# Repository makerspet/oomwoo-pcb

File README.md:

<div align="center">

# OOMWOO I/O Board

*Open-source robot vacuum you build yourself.*

STM32G473 MCU · Motor drivers · Sensors · 4S charging · Smartphone compute (v1) · Raspberry Pi CM4/CM5 (planned) · KiCad

</div>

Part of [OOMWOO open-source robot vacuum](https://github.com/makerspet/oomwoo) project.

Get [MCU firmware](https://github.com/makerspet/oomwoo-firmware/).

## Two boards

I'm keeping the first board as simple as possible, so it can be built and tested sooner:

- **[`kicad/main-phone`](kicad/main-phone/README.md) - v1, in progress.** An Android phone is the compute, connected to the STM32 over USB-C. No Raspberry Pi, cameras, M.2, SD card, speaker or mopping. The STM32 runs every motor and sensor, including the LiDAR and the front ToF sensors, and forwards their data to the phone.
- **[`kicad/main`](kicad/main) - Raspberry Pi CM4/CM5 carrier, planned.** The Pi is still in the plans: cameras, an NPU and always-on Wi-Fi come with it. The notes below describe this board.

Details for both are in the [I/O board spec](docs/SPEC.md). Symbol, footprint and 3D libraries shared by all boards are in [`kicad/lib`](kicad/lib). Each board folder keeps its schematic PDF and BOM in `output/`, e.g. [the v1 board schematic](kicad/main-phone/output/Main.pdf).

The v1 board comes with a **[charging-only dock](kicad/charging-dock/README.md)**: a 20 V brick, a CH32V003 MCU (Arduino core, ch32fun, PlatformIO), robot detection before the contacts go live, and an IR beacon. The plan is to make the v1 board, the dock and the small sensor boards (including the two [front ToF boards](kicad/front-sensors/README.md), one design fitted twice, the [side sensor board](kicad/side-sensors/README.md) six [cliff sensor boards](kicad/cliff-sensor/README.md), the [rear docking IR board](kicad/rear-ir/README.md) and two [Hall sensor boards](kicad/hall-sensor/README.md)) as one panel (V-cuts or mouse bites), so they share parts and cost less to make and ship. To keep part references unique across boards, every board has its own reference range: main board 1-999, dock 1000s, front ToF 2000s, side sensor 3000s, cliff 4000s, rear IR 5000s, Hall 6000s.

## Architecture notes

Consumer vacuums typically split compute into CPU and MCU. The MCU ([real examples](https://robotinfo.dev/)) controls
- all motors - driving wheels, suction fan, side brushes, mop motors, mop lift servos, pump and so on
- all sensors except below - IR cliff, IR side proximity, IR docking, wheel drop, bumper (IR or micro-switches), motor encoders, ultrasonic carpet sensor
- all push buttons
- 2D LiDAR motor RPM
- power - battery charging, motors power on/off
- all safety sensors - overcurrent for all motors (cheap vacuums ignore overcurrent sensing)

I/O board also provides audio encoders/decoders, amp, speaker (connector), mics (if any).

CPU receives
- 2D LiDAR data over serial port
- IMU (sometimes IMU gets forwarded via MCU) over SPI/I2C
- cameras (2x MIPI for visual obstacle avoidance)

MCU (and CPU) are usually always active. This allows the user to start cleaning at any time (especially via app remotely). Exceptions:
- no power (battery dead and no dock power)
- user explicitly shut down the vacuum by long-pressing the power button

The MCU's overarching constraint is to ensure robot safety. This is necessary to pass CE mark tests. Here is how MCU ensures safety:
- MCU firmware uses FreeRTOS or similar, static memory allocation, watchdog, guaranteed reaction time
- MCU acts as watchdog for CPU, resets CPU if CPU becomes unresponsive
- MCU connects to CPU over serial using a custom serial protocol ([concrete example](https://github.com/codetiger/VacuumRobot)). No micro-ROS to reduce dependencies, prevent bugs from updated 3rd party libraries slipping into safety-critical MCU firmware.
- MCU shuts down some (or all) motors when MCU detects overcurrent (brush stuck)
- MCU shuts down all motors (including power to all motors) when CPU becomes unresponsive (to prevent CPU sending garbage commands to MCU)
- MCU monitors battery charging, shuts it down when needed (battery too hot)
- MCU stops driving wheel motors when bumper sensors activate
- MCU tests motors, sensors
- MCU does not depend on CPU
- MCU toggles watchdog GPIO; otherwise an external-to-MCU circuit shuts down motor power

Consumer vacuums place CPU and MCU on the same PCB board. Since OOMWOO has to be hackable, it seems best to separate I/O from the compute. Therefore, this I/O board needs to have
- MCU and programming header
  - STM32G473VCT6 (LQFP-100): enough GPIOs, timers and ADCs for every motor and sensor, built-in op-amps for the carpet sensor echo, a USB device port and an RTC, in a hand-solderable package
  - see the [I/O board spec](docs/SPEC.md)
- all vacuum motor drivers (with connectors), driven by the MCU
  - cliff, side proximity, docking, bumper, carpet, water tank full/empty, dust bin present, motor overcurrent, motor encoders
- MCU connected to all sensors (except those handled by CPU like LiDAR serial, MIPI cameras I/O, IMU); sensor connectors
- control circuit for 2D LiDAR's motor (controlled by MCU)
- battery charging, power management (motors power on/off, charging on/off, power shut down), power for CPU compute module (see below)
- push buttons (home, power, etc.) and UI LEDs
- dock connector (dock power, sense dock present)
- USB power for charging; USB for serial shell, etc.
- audio encoder/decoder, audio amp, mics (if any)
- SD card for hacking, cheap large storage
- connect IMU FSYNC to MCU to synchronize MCU timestamps with IMU data streaming to CPU

Consumer vacuums usually don't have a CPU fan/heatsink because the vacuum's suction fan can (indirectly) cool the CPU/MCU PCB. Therefore, no CPU fan on this I/O board.

As far as compute - currently it seems best to use a Raspberry Pi CM4/CM5 compute module. Why?
- CM4/CM5 modules cost a bit less than a full Raspberry Pi 4/5
- CM4/CM5 have lower profile/height vs a full Raspberry Pi 4/5, important to keep vacuum cleaner slim
- there are plenty of 3rd party compute modules pin-compatible with CM4/CM5, making the compute swappable, hackable
  - 3rd party compute modules with NPUs are especially interesting because we need NPU for real-time camera-based obstacle detection

Compute module headers should expose
- 2x MIPI camera I/O
- 1x serial for CPU-MCU comms
- 1x serial for CPU-LiDAR comms
- 1x SPI (or I2C) for CPU-IMU comms
- audio (digital?) I/O
- power from I/O board to CM
- a few TBD GPIOs
  - MCU GPIO to reset CPU

This board should be designed using an open-source PCB tool (KiCad seems like a good choice).

## No manufacturing support

These designs are shared as-is, for reference and for your own work. I don't support manufacturing them: I can't help with ordering (JLCPCB or otherwise), out-of-stock parts, part substitutions, or troubleshooting boards built by others.

## License

[Apache License 2.0](LICENSE).

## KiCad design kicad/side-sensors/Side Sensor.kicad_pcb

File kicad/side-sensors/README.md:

# OOMWOO side sensor board

A small board on the robot's right side, for wall-following and for spotting the dock while driving past it. It plugs into the [main board](../main-phone/README.md) (SIDE-R1) with a 7-pin cable. Rev 2, 2026-10-27. There is no left side sensor on v1.

Rev 1 had a VL6180 with a 2.8 V regulator and a TSOP38238. The VL6180 is NRND at ST (obsolete at DigiKey and Future), and its 2.8 V I/O sits at its limit on the robot's 3.3 V bus.

## Circuit

- U3001: VL53L0X (VL53L0CXV0DH/1, LCSC C91199, ~$1.63): single-zone time-of-flight distance sensor, runs from 3.3 V directly.
  - It reads poorly below ~3 cm, so the board sits a little recessed in the robot's side.
  - 10 µF + 100 nF (C3001/C3002) at its supply pins.
  - XSHUT has no pull-up since 2026-11-04 (R3001 removed): the MCU drives it (PE3), and the sensor rail is off whenever the MCU is in reset. GPIO1 (open drain, the interrupt) has no pull-up here since 2026-11-03: it joins the shared INT-SENSORS line on the main board, pulled up there by R2 (47k; R61 until 2026-11-11), so R3002 was in parallel with it and is removed. The I2C pull-ups (2.2k) are on the main board too.
  - Firmware: the I/Os run at 3.3 V (= AVDD), so set the ST API to 2V8 I/O mode (the API default is 1V8).
- U3002: Everlight IRM-H638T/TR2 (C91447, ~$0.13), a 38 kHz top-looking IR receiver (the lens is on its top face), the same part as the dock's U1202. It sees the dock's beacon when the robot passes alongside it. Supply filter per the datasheet: R3003 100 Ω + C3003 10 µF. The output has an internal pull-up.

Both parts look out of the board face, so the board mounts upright in the side of the robot, facing out.

## Connector J3001

ZX-SH1.0-7PWT (C7430449): JST SH compatible, 1.0 mm pitch, SMD, right angle. The main board's SIDE-R1 uses the same part.

| Pin | Signal | Main board |
| --- | --- | --- |
| 1 | 3.3 V | |
| 2 | GND | |
| 3 | IR_OUT | PD6 (USART2 RX) |
| 4 | GPIO1 (interrupt) | PD12, shared with the front ToF interrupts (open drain) |
| 5 | XSHUT | PE3 |
| 6 | SCL | I2C4 SCL (PC6) |
| 7 | SDA | I2C4 SDA (PC7) |
| 8, 9 | mounting pads, GND | |

Use a pin 1 to pin 1 cable and mark pin 1 on the silkscreen of both boards.

The VL53L0X starts at I2C address 0x52, the same as the two front VL53L7s on the same bus. Only the left VL53L7's LPn is on the MCU, so XSHUT takes part in addressing: at boot, hold the left LPn and XSHUT low, so only the right VL53L7 answers, and move it to a new address. Release the left LPn and move the left sensor, then release XSHUT; the VL53L0X can keep 0x52. XSHUT also resets a stuck sensor.

## PCB notes (for layout)

- The PCB file in this folder is the old layout. Run *Update PCB from Schematic* before layout work.
- H3001/H3002: two M2 holes (`MountingHole_2.2mm_M2_Pad`, pads to GND, not in the BOM), to keep the board small.
- Keep copper, silkscreen and parts out of the sensor's field of view, and give it a cover window (ST's cover-glass guidance applies).
- Reference designators are in this board's 3000s range: every board has its own reference range: main board 1-999, dock 1000s, front ToF 2000s, side sensor 3000s, cliff 4000s, rear IR 5000s, Hall 6000s.

All parts are assembled at JLC.

Symbols and footprints come from the shared libraries in [`../lib`](../lib) (`JLCImport`) and the KiCad standard libraries.

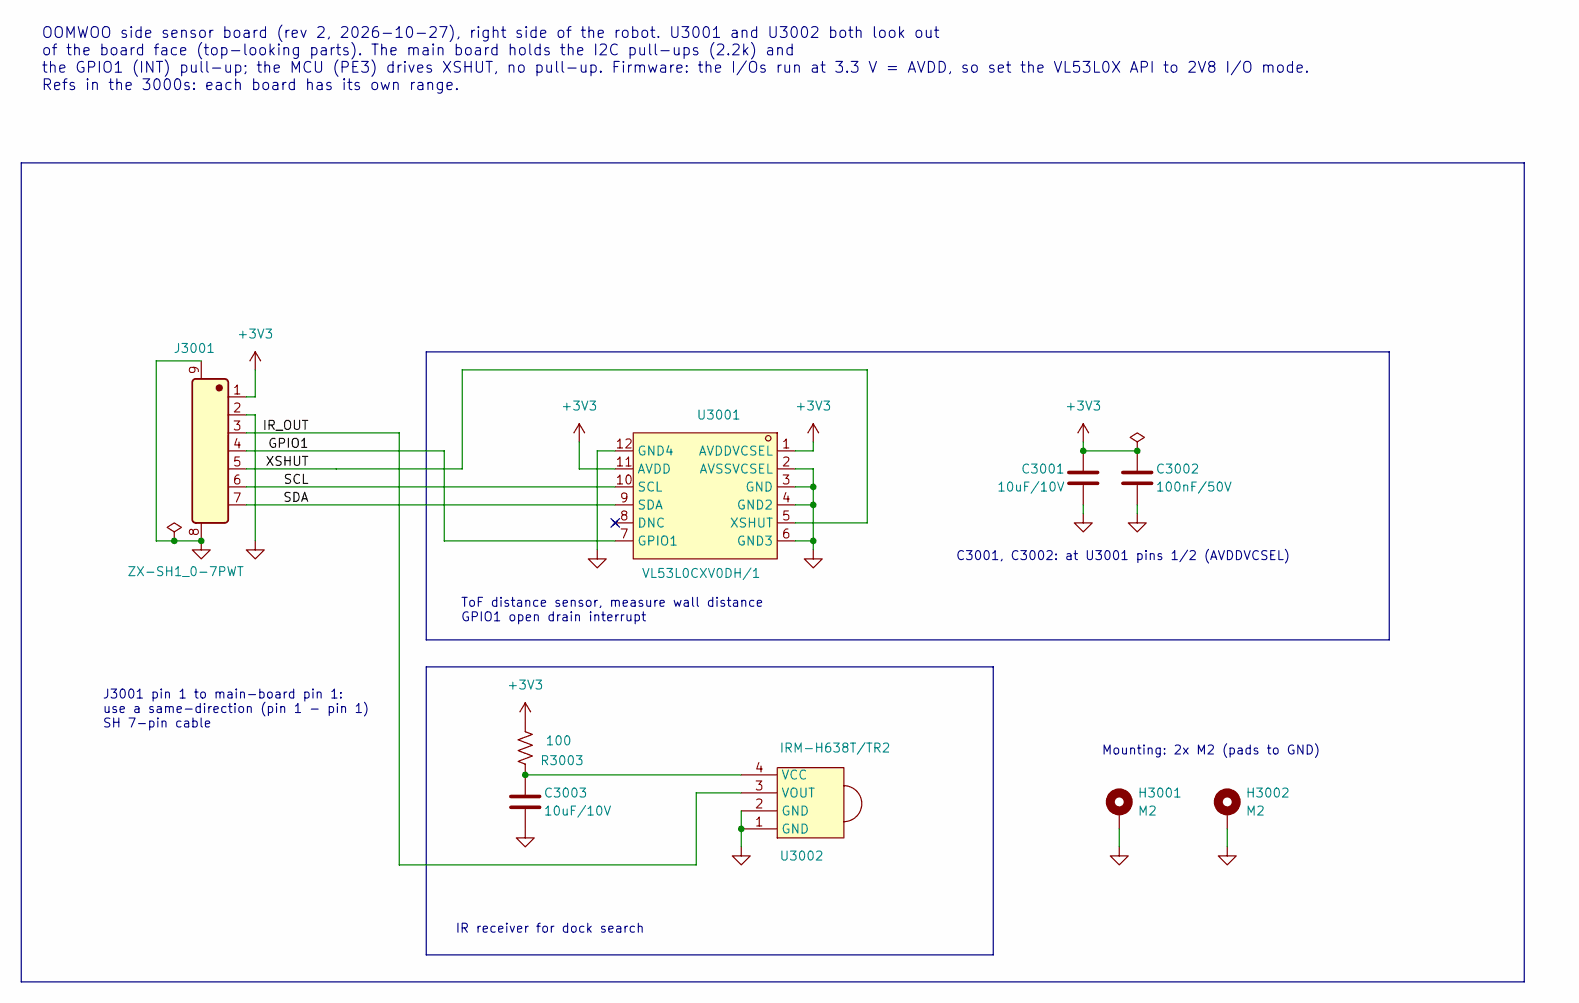
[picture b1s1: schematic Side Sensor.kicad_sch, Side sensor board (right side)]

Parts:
C3001, C3003: 10uF/10V; C_0603_1608Metric; LCSC C19702
C3002: 100nF/50V; C_0603_1608Metric; LCSC C1591
H3001, H3002: M2; MountingHole_2.2mm_M2_Pad
J3001: ZX-SH1_0-7PWT; LCSC C7430449
R3003: 100; R_0603_1608Metric; LCSC C2906981
U3001: VL53L0CXV0DH/1; VL53L0CXV0DH_1; LCSC C91199
U3002: IRM-H638T/TR2; IRM-H638T; LCSC C91447

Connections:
+3V3: C3001.1, C3002.1, J3001.1, R3003.1, U3001.1 (AVDDVCSEL), U3001.11 (AVDD)
/GPIO1: J3001.4, U3001.7 (GPIO1)
/IR_OUT: J3001.3, U3002.3 (VOUT)
/SCL: J3001.6, U3001.10 (SCL)
/SDA: J3001.7, U3001.9 (SDA)
/XSHUT: J3001.5, U3001.5 (XSHUT)
GND: C3001.2, C3002.2, C3003.2, H3001.1 (1_1), H3002.1 (1_1), J3001.2, J3001.8, J3001.9, U3001.2 (AVSSVCSEL), U3001.3 (GND), U3001.4 (GND2), U3001.6 (GND3), U3001.12 (GND4), U3002.1 (GND), U3002.2 (GND)
unnamed: C3003.1, R3003.2, U3002.4 (VCC)

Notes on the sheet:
Mounting: 2x M2 (pads to GND)
C3001, C3002: at U3001 pins 1/2 (AVDDVCSEL)
ToF distance sensor, measure wall distance GPIO1 open drain interrupt
IR receiver for dock search
OOMWOO side sensor board (rev 2, 2026-10-27), right side of the robot. U3001 and U3002 both look out of the board face (top-looking parts). The main board holds the I2C pull-ups (2.2k) and the GPIO1 (INT) pull-up; the MCU (PE3) drives XSHUT, no pull-up. Firmware: the I/Os run at 3.3 V = AVDD, so se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
J3001 pin 1 to main-board pin 1: use a same-direction (pin 1 - pin 1) SH 7-pin cable

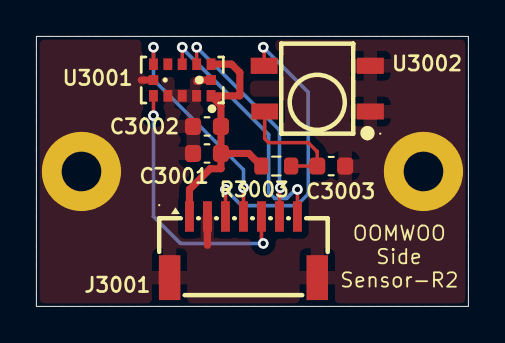
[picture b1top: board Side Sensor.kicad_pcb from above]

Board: 2 copper layers, 24.0 x 15.0 mm, 9 parts (0 on the bottom side), 8 nets.

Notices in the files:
README.md:
License: Apache-2.0
